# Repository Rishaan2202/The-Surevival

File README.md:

# The-Surevival

<h2> Intro!!! </h2>
Yooo there!!! I am Rishaan Sharma, a 14 year old Indian. I made this project, 'The Surevival' as a project in hcb!
<br>
I have made this on KiCad, and yeah I'm a beginner! It's a very interesting project, which was attained after repetitive feilures, so please do check out for the Journal to know all that in detail!

<h2>OVERVIEW 🤔</h2>
So this is gonna be a project on a PCB, which is a PCBA (Yeah, cause I don't even have a soldering iron!), and yeah, It's my first PCB!!! It is basically a tool whose name suggests that it's a 'Survival Tool' (Sure + Survival = SUREVIVAL). Yeah, cool name rigth, ik! This is supposed to have a few features which are listed below! I have used the ESP32-S3FN8 as the MCU! and am having a Type-C input which is just for charging the battery! The 2000mAh Li-ion battery is gonna power up all the stuff like the load sensor, temp. sensor etc... So yeah, It's a cool thing and now take a look at it's features!!!

<h2>FEATURES ⚡️</h2>
1) GPS Tracking 
<br>
2) No. of Survival Dayzzz prediction using food! (My favorite)
<br>
3) Weather Monitoring
<br>
4) OLED Display!!! (For better UI)

<h2> THE SCHEMATIC </h2>

[The Surevival (2).pdf](https://github.com/user-attachments/files/23728820/The.Surevival.2.pdf)

<h3>It consists of 4 units, and These units further contain subunits which are lister below:</h3>
<br>

<h3>1) MCU!!! </h3>
<br>

<h3> 2) Power Management: </h3>
- Input Processing Unit (IPU) <br>
- Buck-Boost converter <br>
- Battery Charging Unit (BCU)
<br>

<h3> 3) Peripherals: </h3>
-Load Sensing Unit (Weight Sensor) <br>
- Switches (UI bro!) <br>
- GPS (ofc.) <br>
- Weather Monitoring Unit (WMU) <br>
- Display (OLED)
<br>

<h3>4) Crystal!</h3>
<br>

<h2>THE PCB</h2>

<h3> SO this is all the placement and routing stuff! It was really Time-Consuming!!! </h3>

<br>

<h3> idts that I need to explain a lot about the PCB, but yeah, I must compliment it's compactness, cause it's just 23mm*51mm </h3>
<br>
<br>

<h2>THE 3D Look (My fav!)</h2>

<h3> So yeah, I kinda like this part, cause it shows how would it be looking when it comes outside the screen (im in real world)! </h3>

<h3> Let's take a look at the one without much of the components, but with the OLED, which was placed by me on KiCad! </h3>

<br>

<br>

<h3> Now, let's see the one with all the components on it except the OLED and the GPS, which was produced by JLCPCB! </h3>
<br>

<h3> Yeah, that's so cool! I can't even believe that I made that! </h3>
<br>
<br>

<h2>THE BOM</h2>

<h3> Hmmm, so here is the tricky part! It took me many days to make this thing! I also tried to add a soldering kit to this, as I need that to put a few components on this, but then I came to know that I can't do that , so I removed that and now the BOM is $86.28 (JLCPCB) + $13.52 (Robocraze). Yeah I have 2 suppliers, one for PCBA and the other for some extra components which has $0 as it is originally from INDIA (As I am!) </h3>
<br>

<h3> Well, this doesn't contain the price of the PCBA products, but that will be clear by looking at this </h3>
<br>

<br>
<br>

<h2>Images</h2>
<br>
<h3>
  
  <br>
  
  <br>
  
  <br>
  
  <br>
</h3>

<h2>OUTRO!!!</h2>
<br>

Yeah, so this was the first PCB built by me, I have already made one before, but because of some unignorable things, I will need to redesign it. Well if you want to give any kinda comment regarding this project, then pls feel free to contact me. Here are my details:
<br>

Slack Username (Hackclub Workflow): @Rishaan
<br>
Email: rishaan.sharma2202@gmail.com

Pls don't forget to take a look at the journals! And also pls visit and follow this project on Blueprint here:
<br>

https://blueprint.hackclub.com/projects/210
<br>
<h2> TYSM 😊🙏 </h2>

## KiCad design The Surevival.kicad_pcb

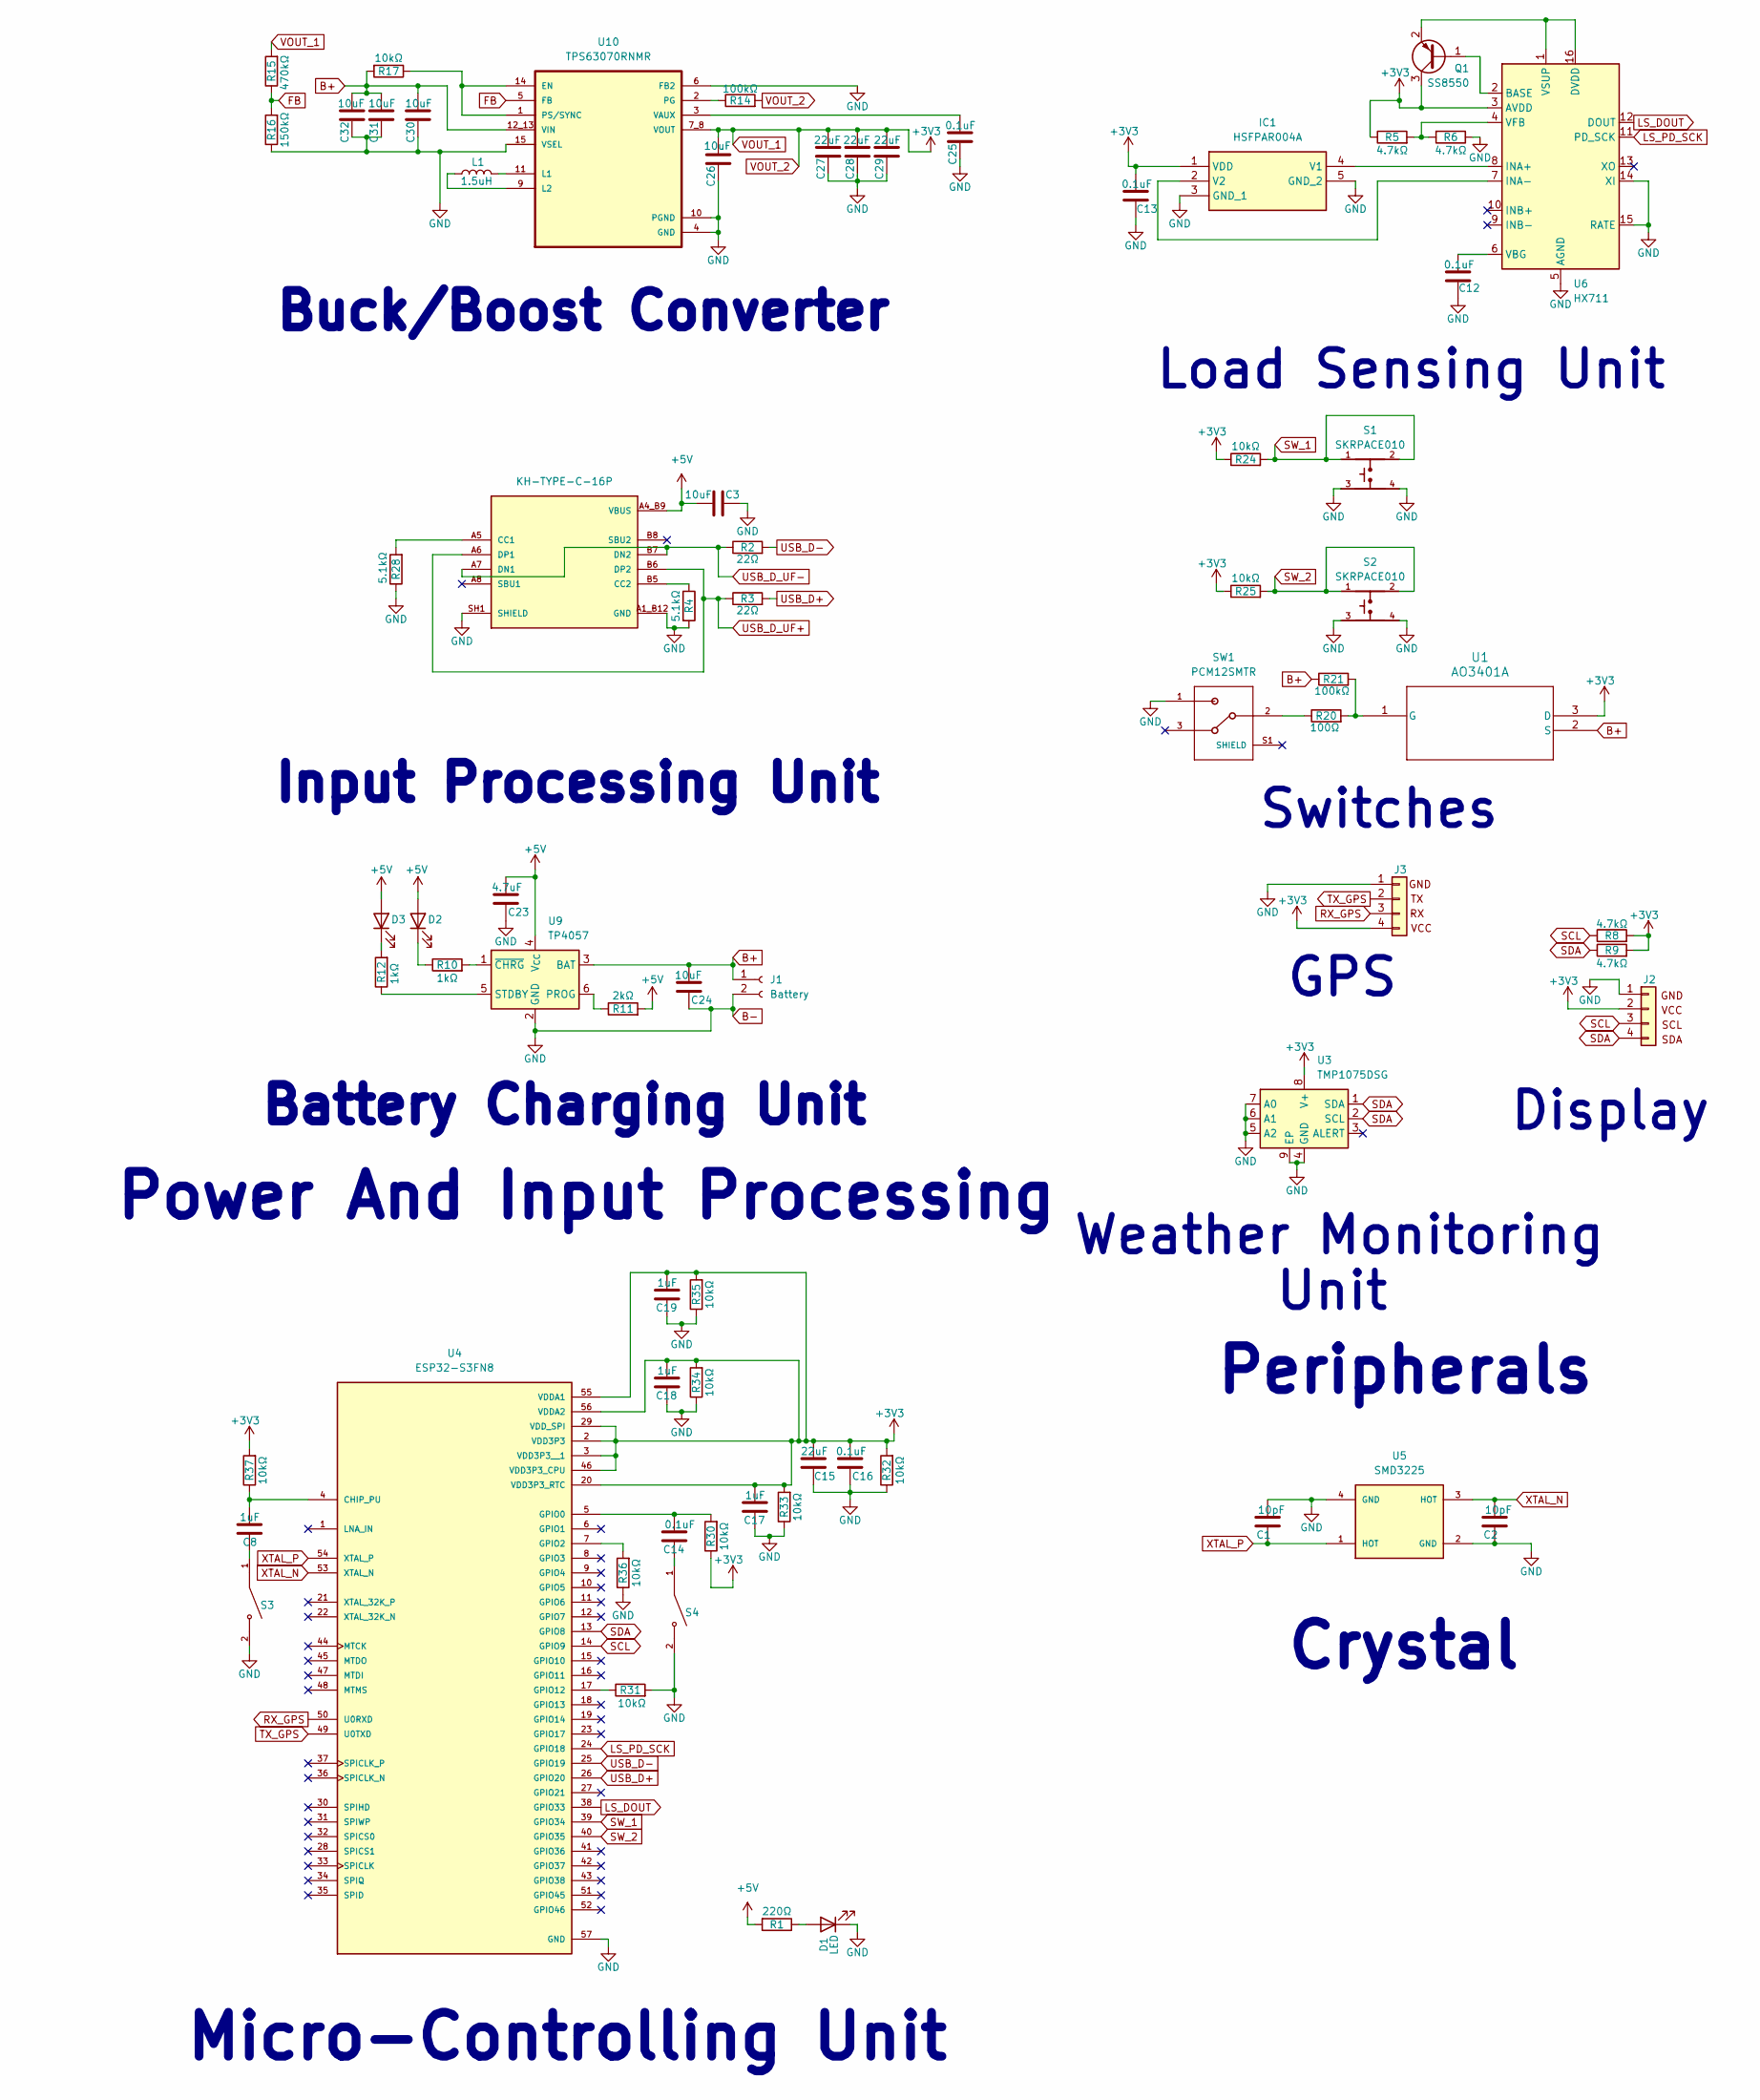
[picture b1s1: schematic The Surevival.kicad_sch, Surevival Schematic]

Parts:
C1, C2: 10pF; C_0402_1005Metric
C3, C24, C26, C30, C31, C32: 10uF; C_0402_1005Metric
C8, C17, C18, C19: 1uF; C_0402_1005Metric
C12, C13, C14, C16, C25: 0.1uF; C_0402_1005Metric
C15, C27, C28, C29: 22uF; C_0402_1005Metric
C23: 4.7uF; C_0402_1005Metric
D1, D2, D3: LED; LED_0402_1005Metric
IC1: HSFPAR004A; Mouser Part Number 688-HSFPAR004A
J1: Battery; PinHeader_1x02_P2.54mm_Vertical
J2, J3: Conn_01x04; PinHeader_1x04_P2.54mm_Vertical
J6: KH-TYPE-C-16P; KINGHELM_KH-TYPE-C-16P; PARTREV A0
L1: 1.5uH; L_0805_2012Metric
Q1: SS8550; SOT-23
R1: 220Ω; R_0402_1005Metric
R2, R3: 22Ω; R_0402_1005Metric
R4, R28: 5.1kΩ; R_0402_1005Metric
R5, R6, R8, R9: 4.7kΩ; R_0402_1005Metric
R10, R12: 1kΩ; R_0402_1005Metric
R11: 2kΩ; R_0402_1005Metric
R14, R21: 100kΩ; R_0402_1005Metric
R15: 470kΩ; R_0402_1005Metric
R16: 150kΩ; R_0402_1005Metric
R17, R24, R25, R30, R31, R32, R33, R34, R35, R36, R37: 10kΩ; R_0402_1005Metric
R20: 100Ω; R_0402_1005Metric
S1, S2: SKRPACE010; SW_SKRPACE010
S3, S4: TS-1088-AR02016; Push Button; PARTREV N/A
SW1: PCM12SMTR; SW_PCM12SMTR
U1: AO3401A; SOT-23-3L_AOS
U3: TMP1075DSG; WSON-8-1EP_2x2mm_P0.5mm_EP0.9x1.6mm_ThermalVias
U4: ESP32-S3FN8
U5: SMD3225; Crystal_SMD_3225-4Pin_3.2x2.5mm
U6: HX711; SOP-16_3.9x9.9mm_P1.27mm
U9: TP4057; SOT23-6
U10: TPS63070RNMR; VREG_TPS63070RNMR

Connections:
+5V: C3.1, C23.1, D2.2 (A), D3.2 (A), J6.A4_B9 (VBUS), J6.A9_B4 (VBUS), R1.2, R11.2, U9.4 (V_{CC})
B+: C24.1, C30.2, C31.2, C32.2, J1.1, R17.2, R21.1, U1.2 (S), U9.3 (BAT), U10.12_13 (VIN)
B-: C1.1, C2.2, C3.2, C12.2, C13.2, C15.2, C16.2, C17.2, C18.2, C19.2, C23.2, C24.2, C25.1, C26.1, C27.1, C28.1, C29.1, C30.1, C31.1, C32.1, D1.1 (K), IC1.3 (GND_1), IC1.5 (GND_2), J1.2, J2.1, J3.1, J6.A1_B12 (GND), J6.A12_B1 (GND), J6.SH1 (SHIELD), J6.SH2 (SHIELD), J6.SH3 (SHIELD), J6.SH4 (SHIELD), R4.2, R6.1, R16.1, R28.1, R31.2, R32.1, R33.1, R34.1, R35.1, R36.1, S1.3, S1.4, S2.3, S2.4, S3.2, S4.2, SW1.1, U3.4 (GND), U3.5 (A2), U3.6 (A1), U3.7 (A0), U3.9 (EP), U4.57 (GND), U5.2 (GND), U5.4 (GND), U6.5 (AGND), U6.14 (XI), U6.15 (RATE), U9.2 (GND), U10.4 (GND), U10.6 (FB2), U10.10 (PGND), U10.15 (VSEL)
FB: R15.1, R16.2, U10.5 (FB)
LS_DOUT: U4.38 (GPIO33), U6.12 (DOUT)
LS_PD_SCK: U4.24 (GPIO18), U6.11 (PD_SCK)
unnamed: C8.2, S3.1
unnamed: C14.2, S4.1
unnamed: D1.2 (A), R1.1
unnamed: D2.1 (K), R10.1
unnamed: D3.1 (K), R12.2
unnamed: IC1.4 (V1), U6.8 (INA+)
unnamed: IC1.2 (V2), U6.7 (INA-)
unnamed: J6.A5 (CC1), R28.2
unnamed: J6.B5 (CC2), R4.1
unnamed: Q1.1 (B), U6.2 (BASE)
unnamed: Q1.2 (E), U6.1 (VSUP), U6.16 (DVDD)
unnamed: R20.1, SW1.2
unnamed: R20.2, R21.2, U1.1 (G)
unnamed: C8.1, R37.1, U4.4 (CHIP_PU)
unnamed: C14.1, R30.2, U4.5 (GPIO0)
unnamed: R36.2, U4.7 (GPIO2)
unnamed: R31.1, U4.17 (GPIO12)
unnamed: C12.1, U6.6 (VBG)
unnamed: R5.2, R6.2, U6.4 (VFB)
unnamed: R11.1, U9.6 (PROG)
unnamed: R12.1, U9.5 (STDBY)
unnamed: R10.2, U9.1 (~CHRG)
unnamed: R17.1, U10.1 (PS/SYNC), U10.14 (EN)
unnamed: L1.2, U10.11 (L1)
unnamed: L1.1, U10.9 (L2)
unnamed: R14.1, U10.2 (PG)
unnamed: C25.2, U10.3 (VAUX)
RX_GPS: J3.3, U4.50 (U0RXD)
SCL: J2.3, R8.1, U4.14 (GPIO9)
SDA: J2.4, R9.1, U3.1 (SDA), U3.2 (SCL), U4.13 (GPIO8)
SW_1: R24.2, S1.1, S1.2, U4.39 (GPIO34)
SW_2: R25.2, S2.1, S2.2, U4.40 (GPIO35)
TX_GPS: J3.2, U4.49 (U0TXD)
USB_D+: R3.2, U4.26 (GPIO20)
USB_D-: R2.2, U4.25 (GPIO19)
USB_D_UF+: J6.A6 (DP1), J6.B6 (DP2), R3.1
USB_D_UF-: J6.A7 (DN1), J6.B7 (DN2), R2.1
VOUT_1: C13.1, C15.1, C16.1, C17.1, C18.1, C19.1, C26.2, C27.2, C28.2, C29.2, IC1.1 (VDD), J2.2, J3.4, Q1.3 (C), R5.1, R8.2, R9.2, R14.2, R15.2, R24.1, R25.1, R30.1, R32.2, R33.2, R34.2, R35.2, R37.2, U1.3 (D), U3.8 (V+), U4.2 (VDD3P3), U4.3 (VDD3P3__1), U4.20 (VDD3P3_RTC), U4.29 (VDD_SPI), U4.46 (VDD3P3_CPU), U4.55 (VDDA1), U4.56 (VDDA2), U6.3 (AVDD), U10.7_8 (VOUT)
XTAL_N: C2.1, U4.53 (XTAL_N), U5.3 (HOT)
XTAL_P: C1.2, U4.54 (XTAL_P), U5.1 (HOT)

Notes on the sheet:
Unit
Switches
Battery Charging Unit
Peripherals
Buck/Boost Converter
GPS
Power And Input Processing
Micro-Controlling Unit
Input Processing Unit
Weather Monitoring
Load Sensing Unit
Display
Crystal

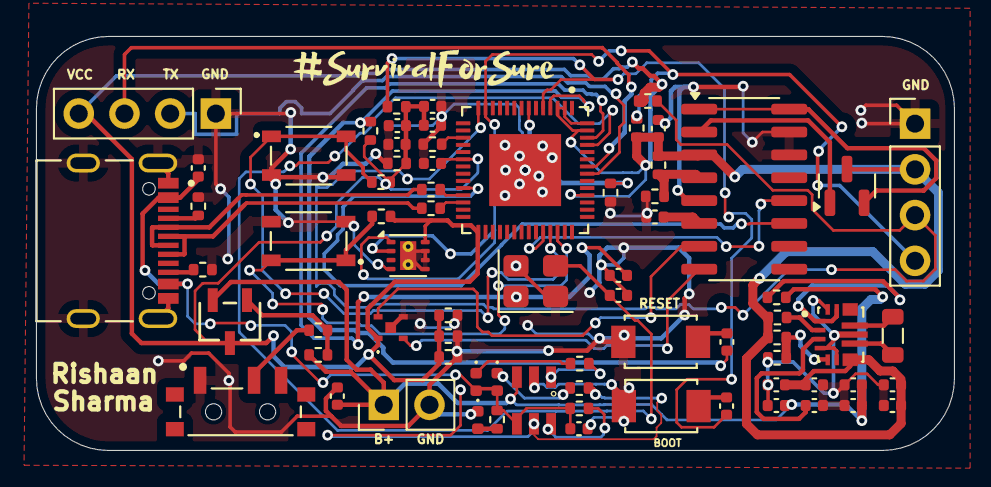
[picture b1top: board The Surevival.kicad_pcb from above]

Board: 2 copper layers, 51.0 x 23.0 mm, 72 parts (0 on the bottom side), 46 nets.

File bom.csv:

Designator,Footprint,Quantity,Value,LCSC Part #,Robocraze,Value (in USD)
"C1, C2",402,2,10pF,C32949,,
"C12, C13, C14, C16, C25, C7",402,6,0.1uF,C1525,,
"C15, C27, C28, C29",402,4,22uF,C105226,,
"C17, C18, C19, C8",402,4,1uF,C52923,,
C23,402,1,4.7uF,C23733,,
"C24, C26, C30, C31, C32, C6",402,6,10uF,C15525,,
"D1, D2, D3",402,3,LED,C30584803,,
IC1,HSFPAR004A,1,HSFPAR004A,C470800,,
J1,PinHeader_1x02_P2.54mm_Vertical_JST,1,Battery Connectors,,2.54mm pitch 2 pin JST Cable with Connector,0.73
"J2, J3",PinHeader_1x04_P2.54mm_Vertical_Female,1,Conn_01x04,,40x1 Female Berg Strip,0.1
J5,AMPHENOL_10155435-00011LF,1,USB Type-C Input,C2765186,,
L1,805,1,1.5uH,C216155,,
Q1,SOT-23,1,SS8550,C727138,,
R1,402,1,220Ω,C25091,,
"R10, R12",402,2,1kΩ,C11702,,
R11,402,1,2kΩ,C4109,,
"R14, R21",402,2,100kΩ,C25741,,
R15,402,1,470kΩ,C427225,,
R16,402,1,150kΩ,C2909320,,
"R17, R24, R25, R30, R31, R32, R33, R34, R35, R36, R37",402,11,10kΩ,C25744,,
"R2, R3",402,2,5kΩ,C5948099,,
R20,402,1,100Ω,C25076,,
"R26, R27",402,2,22Ω,C25092,,
"R28, R29",402,2,5.1kΩ,C25905,,
"R5, R6, R8, R9",402,4,4.7kΩ,C25900,,
"S1, S2",SW_SKRPACE010,2,SKRPACE010,C139797,,
"S3, S4",Push Button,2,TS-1088-AR02016,C720477,,
SW1,SW_PCM12SMTR,1,PCM12SMTR,C221841,,
U1,SOT-23-3L_AOS,1,AO3401A,C15127,,
U10,VREG_TPS63070RNMR,1,TPS63070RNMR,C109322,,
U3,WSON-8-1EP_2x2mm_P0.5mm_EP0.9x1.6mm_ThermalVias,1,TMP1075DSG,C2870250,,
U4,ESP32-S3FN8,1,ESP32-S3FN8,C2913196,,
U5,Crystal_SMD_3225-4Pin_3.2x2.5mm,1,SMD3225,C5444549,,
U6,SOP-16_3.9x9.9mm_P1.27mm,1,HX711,C6705483,,
U9,SOT23-6,1,TP4057,C725791,,
J6,PinHeader_1x04_P2.54mm_Vertical_Male,1,,,40x1 Pin 2.54mm Pitch Male Berg Strip,0.056
Display1,OLED Display,1,,,0.96 Inch OLED Display Module SPI/I2C 4pin Blue Color,3.52
GPS1,GPS,1,,,Ublox Neo-6M GPS Module With EEPROM,5.39
B1,Li-ion Battery,1,Battery,,Witty Fox 3.7V 2000 mAh Li-ion GPS Cylindrical Battery,3.41
,,,,,,13.206

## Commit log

2025-10-06 JOURNAL.md
2025-10-10 ROUGH.md
2025-11-15 Revise project description and features in README
    Updated the README to reflect changes in project description and features.
2025-11-16 Fix heading formatting and enhance README content
    Corrected heading formatting and added new sections with images and descriptions.
2026-03-20 Add images to README section
